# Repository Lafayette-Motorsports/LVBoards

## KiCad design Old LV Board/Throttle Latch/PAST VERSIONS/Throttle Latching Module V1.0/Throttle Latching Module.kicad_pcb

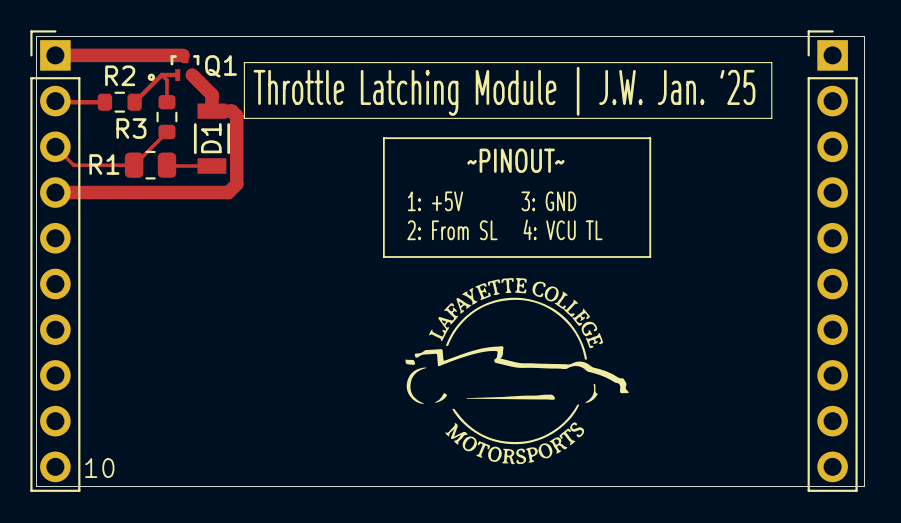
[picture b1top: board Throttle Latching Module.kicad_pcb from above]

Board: 2 copper layers, 46.0 x 25.0 mm, 7 parts (0 on the bottom side), 6 nets.

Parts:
D1: LED (Test); LED_AP3216SYD_KNB
J1, J1#2: PH1-10-UA; PinHeader_1x10_P2.54mm_Vertical
Q1: SSM3J56MFV; VESM_TOS
R1: 150R; R_0805_2012Metric
R2, R3: 10k; R_0603_1608Metric

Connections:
unnamed: D1.2 (A), J1.4, Q1.2 (S)
unnamed: D1.1 (K), R1.2
unnamed: J1.2, R2.1
unnamed: J1.3, R1.1, R3.1
unnamed: J1.1, Q1.3 (D)
unnamed: Q1.1 (G), R2.2, R3.2

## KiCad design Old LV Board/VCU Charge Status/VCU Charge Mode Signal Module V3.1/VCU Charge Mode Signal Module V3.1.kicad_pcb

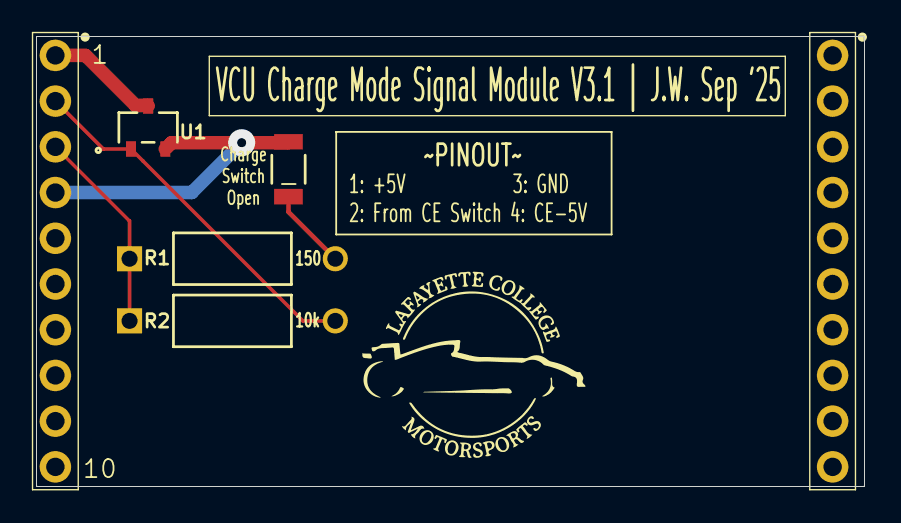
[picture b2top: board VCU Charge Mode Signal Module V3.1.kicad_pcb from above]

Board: 2 copper layers, 46.0 x 25.0 mm, 6 parts (0 on the bottom side), 5 nets.

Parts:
D1: LED (Test); LED_AP3216SYD_KNB
J1, J2: PH1-10-UA; 1X10-2.54MM-THT
R1: 150R; STA_CF14_STP
R2: 10k; STA_CF14_STP
U1: IRLML2060TRPBF; SOT23_INF

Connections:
unnamed: D1.2 (A), J1.4, U1.2 (S)
unnamed: D1.1 (K), R1.2
unnamed: J1.3, R1.1, R2.1
unnamed: J1.1, U1.3 (D)
unnamed: J1.2, R2.2, U1.1 (G)

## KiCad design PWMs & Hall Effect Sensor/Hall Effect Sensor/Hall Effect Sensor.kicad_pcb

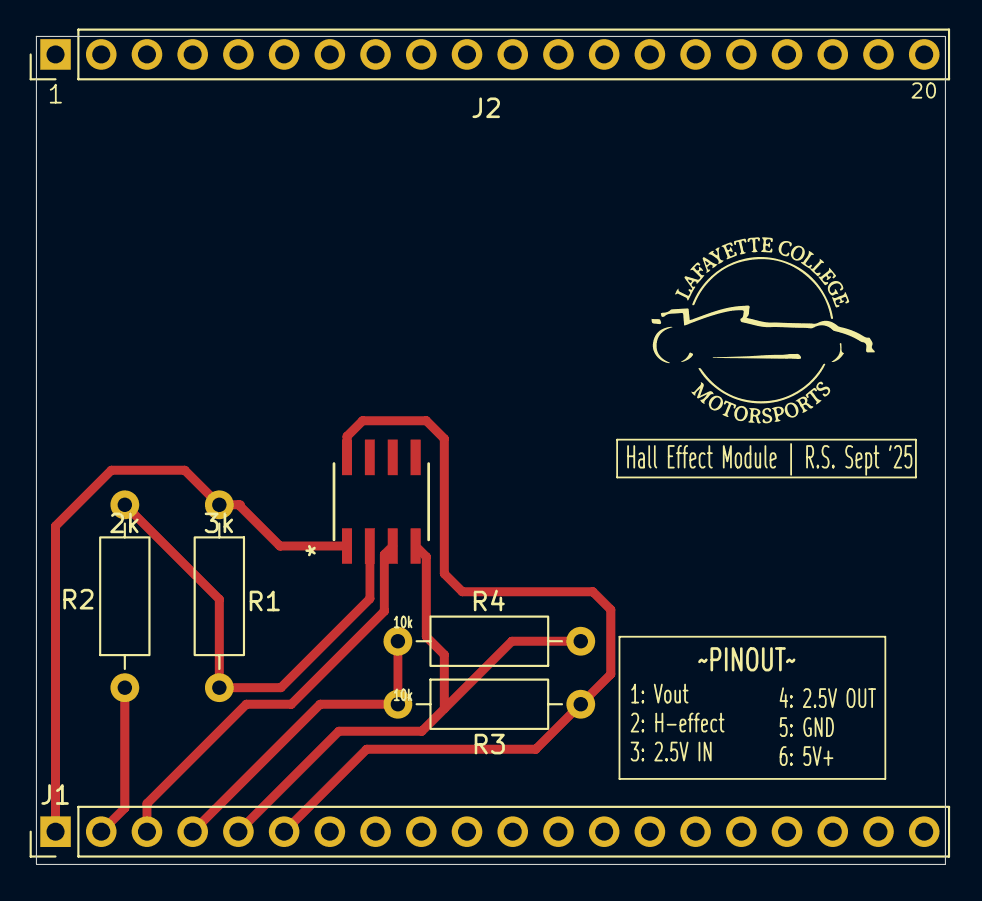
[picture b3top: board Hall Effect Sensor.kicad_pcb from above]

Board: 2 copper layers, 50.5 x 46.0 mm, 7 parts (0 on the bottom side), 7 nets.

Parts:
J1, J2: PH1-20-UA; PinHeader_1x20_P2.54mm_Vertical
R1: 3k; R_Axial_DIN0207_L6.3mm_D2.5mm_P10.16mm_Horizontal
R2: 2k; R_Axial_DIN0207_L6.3mm_D2.5mm_P10.16mm_Horizontal
R3, R4: 10k; R_Axial_DIN0207_L6.3mm_D2.5mm_P10.16mm_Horizontal
opamp1: ADA4510-2ARZ; R-8_ADI

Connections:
+5V in: J1.6, R3.2, opamp1.8 (V+)
GND: J1.5, R4.1, opamp1.4 (V-)
Hall Effect Out: J1.2, R2.1
unnamed: R1.2, R2.2, opamp1.2 (INA-)
V(2.5)OUT: J1.4, R3.1, R4.2
V(2.5V)IN: J1.3, opamp1.3 (INA+)
Vout+: J1.1, R1.1, opamp1.1 (OUTA)

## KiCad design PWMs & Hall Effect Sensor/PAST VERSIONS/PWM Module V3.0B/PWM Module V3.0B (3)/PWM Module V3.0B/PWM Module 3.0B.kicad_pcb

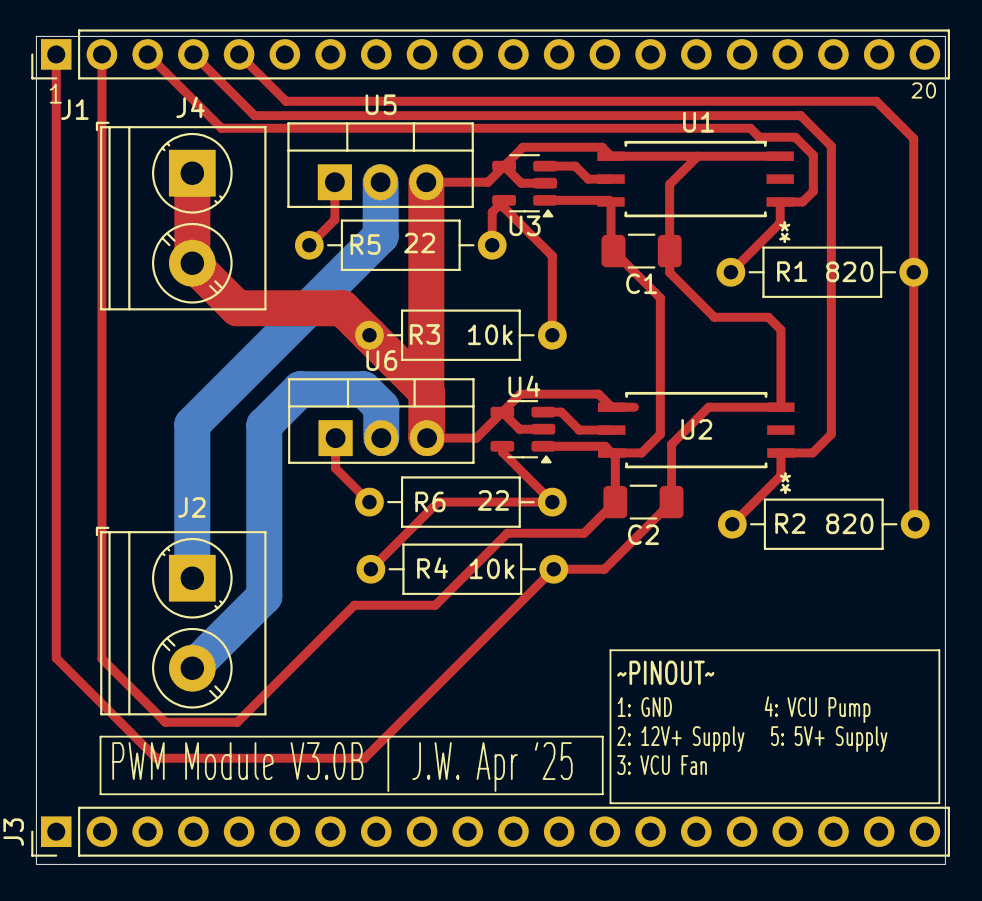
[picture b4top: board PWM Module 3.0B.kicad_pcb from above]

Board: 2 copper layers, 50.5 x 46.0 mm, 18 parts (0 on the bottom side), 13 nets.

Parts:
C1, C2: 0.1u; C_1206_3216Metric_Pad1.33x1.80mm_HandSolder
J1, J3: PH1-20-UA; PinHeader_1x20_P2.54mm_Vertical
J2, J4: Conn_01x02_Pin; TerminalBlock_Phoenix_PT-1,5-2-5.0-H_1x02_P5.00mm_Horizontal
R1, R2: 820; R_Axial_DIN0207_L6.3mm_D2.5mm_P10.16mm_Horizontal
R3, R4: 10k; R_Axial_DIN0207_L6.3mm_D2.5mm_P10.16mm_Horizontal
R5, R6: 22; R_Axial_DIN0207_L6.3mm_D2.5mm_P10.16mm_Horizontal
U1, U2: TLP2745TP_E; SO6L_TOS
U3, U4: UCC27517DBVR; SOT-23-5
U5, U6: IRLZ44NPBF; TO-220-3_Vertical

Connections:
unnamed: J1.3, R1.2, U1.1
unnamed: J1.4, R2.2, U2.1
unnamed: J1.5, R1.1, R2.1
unnamed: J2.1, U5.2 (D)
unnamed: J2.2, U6.2 (D)
unnamed: C1.1, C2.1, J1.1, J4.1, J4.2, R3.2, R4.2, U1.3, U1.4, U2.3, U2.4, U3.2 (GND), U3.4 (IN-), U4.2 (GND), U4.4 (IN-), U5.3 (S), U6.3 (S)
unnamed: U1.5, U3.3 (IN+)
unnamed: R3.1, R5.1, U3.5 (OUT)
unnamed: C1.2, C2.2, J1.2, U1.6, U2.6, U3.1 (VDD), U4.1 (VDD)
unnamed: U2.5, U4.3 (IN+)
unnamed: R4.1, R6.1, U4.5 (OUT)
unnamed: R5.2, U5.1 (G)
unnamed: R6.2, U6.1 (G)
